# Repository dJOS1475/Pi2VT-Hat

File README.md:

# Pi2VT-Hat
Pi2VT Hat v1.0 for VT220 terminals etc

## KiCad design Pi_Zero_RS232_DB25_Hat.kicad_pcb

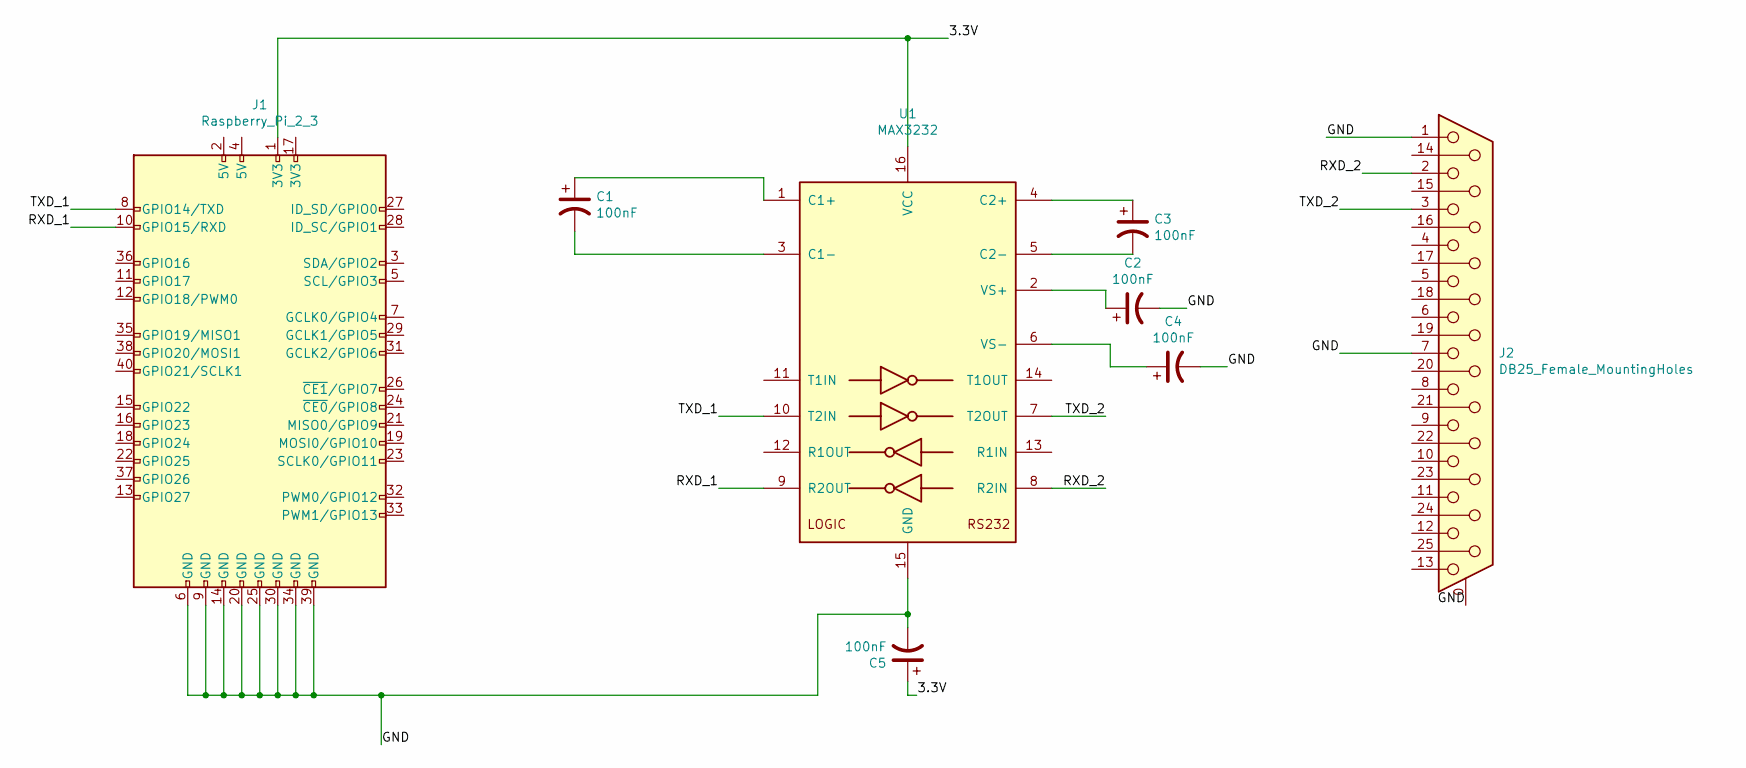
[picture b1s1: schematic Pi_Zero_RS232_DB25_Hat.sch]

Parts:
C1, C2, C3, C4, C5: 100nF; C_0805_2012Metric_Pad1.15x1.40mm_HandSolder
J1: Raspberry_Pi_2_3; PinSocket_2x20_P2.54mm_Vertical
J2: DB25_Female_MountingHoles; DSUB-25_Female_Horizontal_P2.77x2.84mm_EdgePinOffset4.94mm_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
U1: MAX3232; SOIC-16_3.9x9.9mm_P1.27mm

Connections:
/3.3V: C5.1, J1.1 (3V3), U1.16 (VCC)
/GND: C2.2, C4.2, C5.2, J1.6 (GND), J1.9 (GND), J1.14 (GND), J1.20 (GND), J1.25 (GND), J1.30 (GND), J1.34 (GND), J1.39 (GND), J2.0 (PAD), J2.1, J2.7, U1.15 (GND)
/RXD_1: J1.10 (GPIO15/RXD), U1.9 (R2OUT)
/RXD_2: J2.2, U1.8 (R2IN)
/TXD_1: J1.8 (GPIO14/TXD), U1.10 (T2IN)
/TXD_2: J2.3, U1.7 (T2OUT)
unnamed: C1.1, U1.1 (C1+)
unnamed: C1.2, U1.3 (C1-)
unnamed: C2.1, U1.2 (VS+)
unnamed: C3.1, U1.4 (C2+)
unnamed: C3.2, U1.5 (C2-)
unnamed: C4.1, U1.6 (VS-)

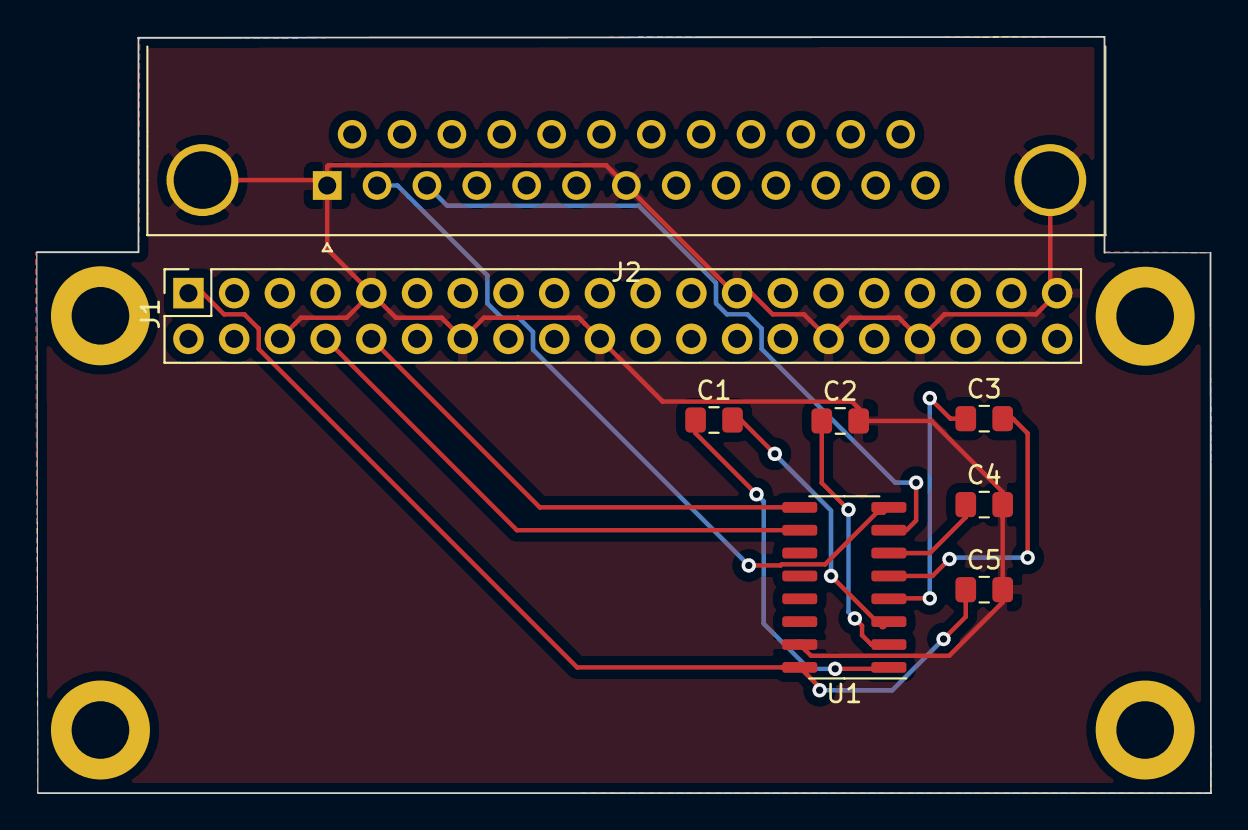
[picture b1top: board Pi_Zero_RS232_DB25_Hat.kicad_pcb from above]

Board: 2 copper layers, 65.2 x 42.0 mm, 8 parts (0 on the bottom side), 12 nets.

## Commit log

2021-04-02 Add files via upload
    Initial Commit
2021-04-19 Updated Design v1.0
